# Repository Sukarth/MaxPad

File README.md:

# MaxPad
My attempt at making a utility keypad with maximum functionality! It's a 5x3 ortholinear macropad featuring a rotary encoder and OLED display, designed for context-aware developer workflows. The custom PCB uses a Xiao RP2040 with a 3x4 matrix layout. Designed in KiCad and OnShape. The full KiCad project files are included in this repository inside [MaxPadProject.zip](MaxPadProject.zip).

Check out the custom built desktop companion/customization app for the MaxPad here: https://github.com/Sukarth/MaxPadApp 

## Images

### MaxPad Case

### MaxPad Full Assembly

### MaxPad PCB Schematic

### MaxPad PCB

### Rendered MaxPad PCB (3D)

## License
MIT. See [LICENSE](LICENSE) for more details.

## Support

If this project helps or saves you time, consider supporting my work, as it keeps projects like this free, open source, and maintained:

Can't donate? Starring the repo ⭐, reporting bugs, and sharing the project help just as much!

---

Built with ❤️ by Sukarth

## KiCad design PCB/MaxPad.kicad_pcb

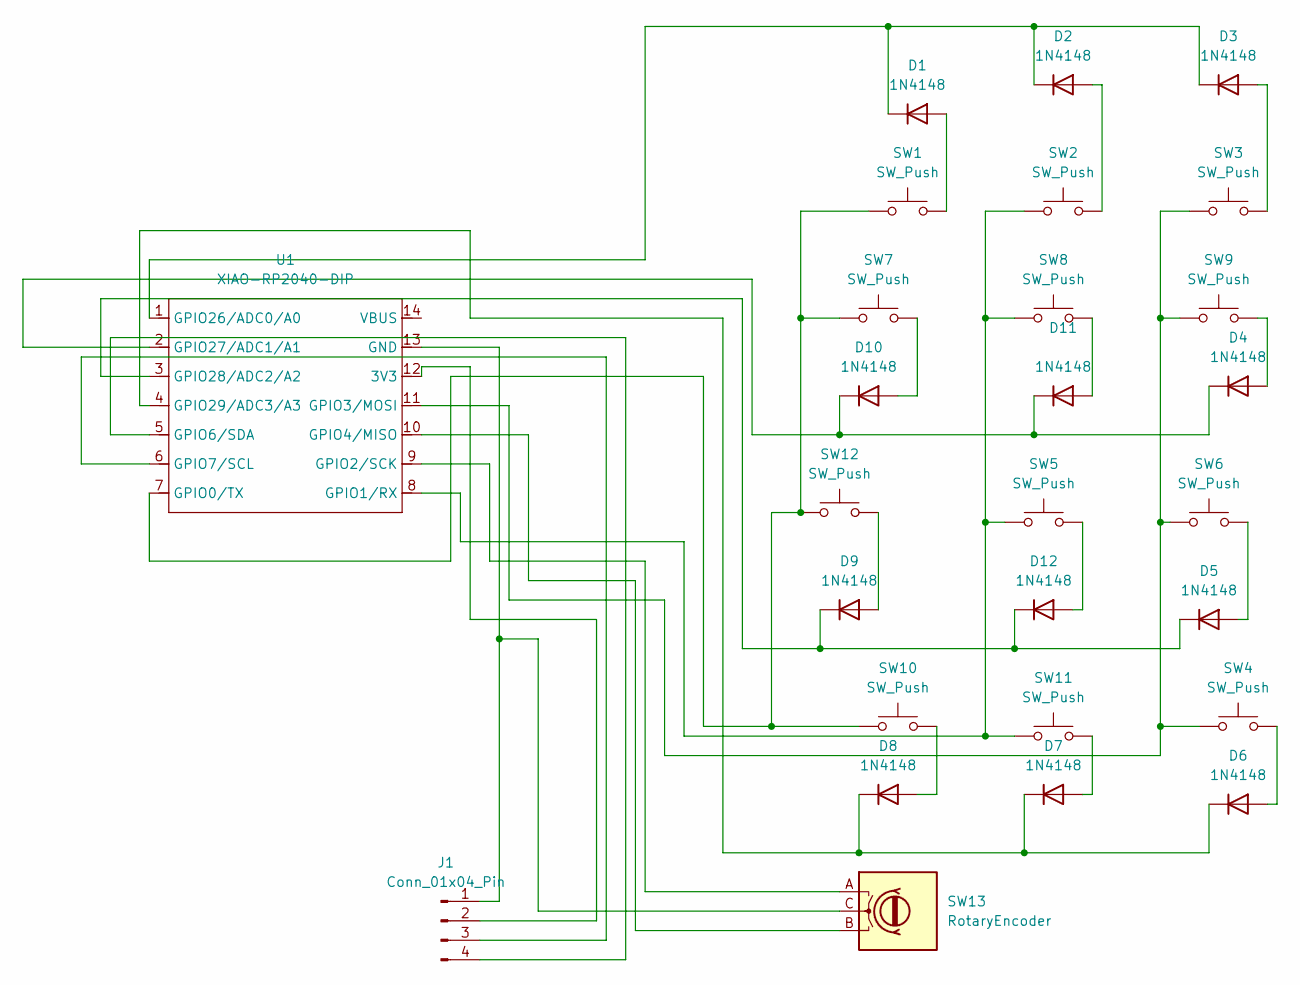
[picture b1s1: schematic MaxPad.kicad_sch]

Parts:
D1, D2, D3, D4, D5, D6, D7, D8, D9, D10, D11, D12: 1N4148; D_DO-35_SOD27_P7.62mm_Horizontal
J1: Conn_01x04_Pin; PinHeader_1x04_P2.54mm_Vertical
SW1, SW2, SW3, SW4, SW5, SW6, SW7, SW8, SW9, SW10, SW11, SW12: SW_Push; SW_Cherry_MX_1.00u_PCB
SW13: RotaryEncoder; RotaryEncoder_Alps_EC11E-Switch_Vertical_H20mm
U1: XIAO-RP2040-DIP

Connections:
unnamed: D1.2 (A), SW1.2
unnamed: D1.1 (K), D2.1 (K), D3.1 (K), U1.1 (GPIO26/ADC0/A0)
unnamed: D2.2 (A), SW2.2
unnamed: D3.2 (A), SW3.2
unnamed: D4.2 (A), SW9.2
unnamed: D5.2 (A), SW6.2
unnamed: D6.2 (A), SW4.2
unnamed: D6.1 (K), D7.1 (K), D8.1 (K), U1.4 (GPIO29/ADC3/A3)
unnamed: D7.2 (A), SW11.2
unnamed: D8.2 (A), SW10.2
unnamed: D9.2 (A), SW12.2
unnamed: D10.2 (A), SW7.2
unnamed: D4.1 (K), D10.1 (K), D11.1 (K), U1.2 (GPIO27/ADC1/A1)
unnamed: D11.2 (A), SW8.2
unnamed: D12.2 (A), SW5.2
unnamed: D5.1 (K), D9.1 (K), D12.1 (K), U1.3 (GPIO28/ADC2/A2)
unnamed: J1.1, SW13.C, U1.13 (GND)
unnamed: J1.2, U1.12 (3V3)
unnamed: J1.3, U1.6 (GPIO7/SCL)
unnamed: J1.4, U1.5 (GPIO6/SDA)
unnamed: SW1.1, SW7.1, SW10.1, SW12.1, U1.7 (GPIO0/TX)
unnamed: SW2.1, SW5.1, SW8.1, SW11.1, U1.8 (GPIO1/RX)
unnamed: SW13.A, U1.9 (GPIO2/SCK)
unnamed: SW3.1, SW4.1, SW6.1, SW9.1, U1.11 (GPIO3/MOSI)
unnamed: SW13.B, U1.10 (GPIO4/MISO)

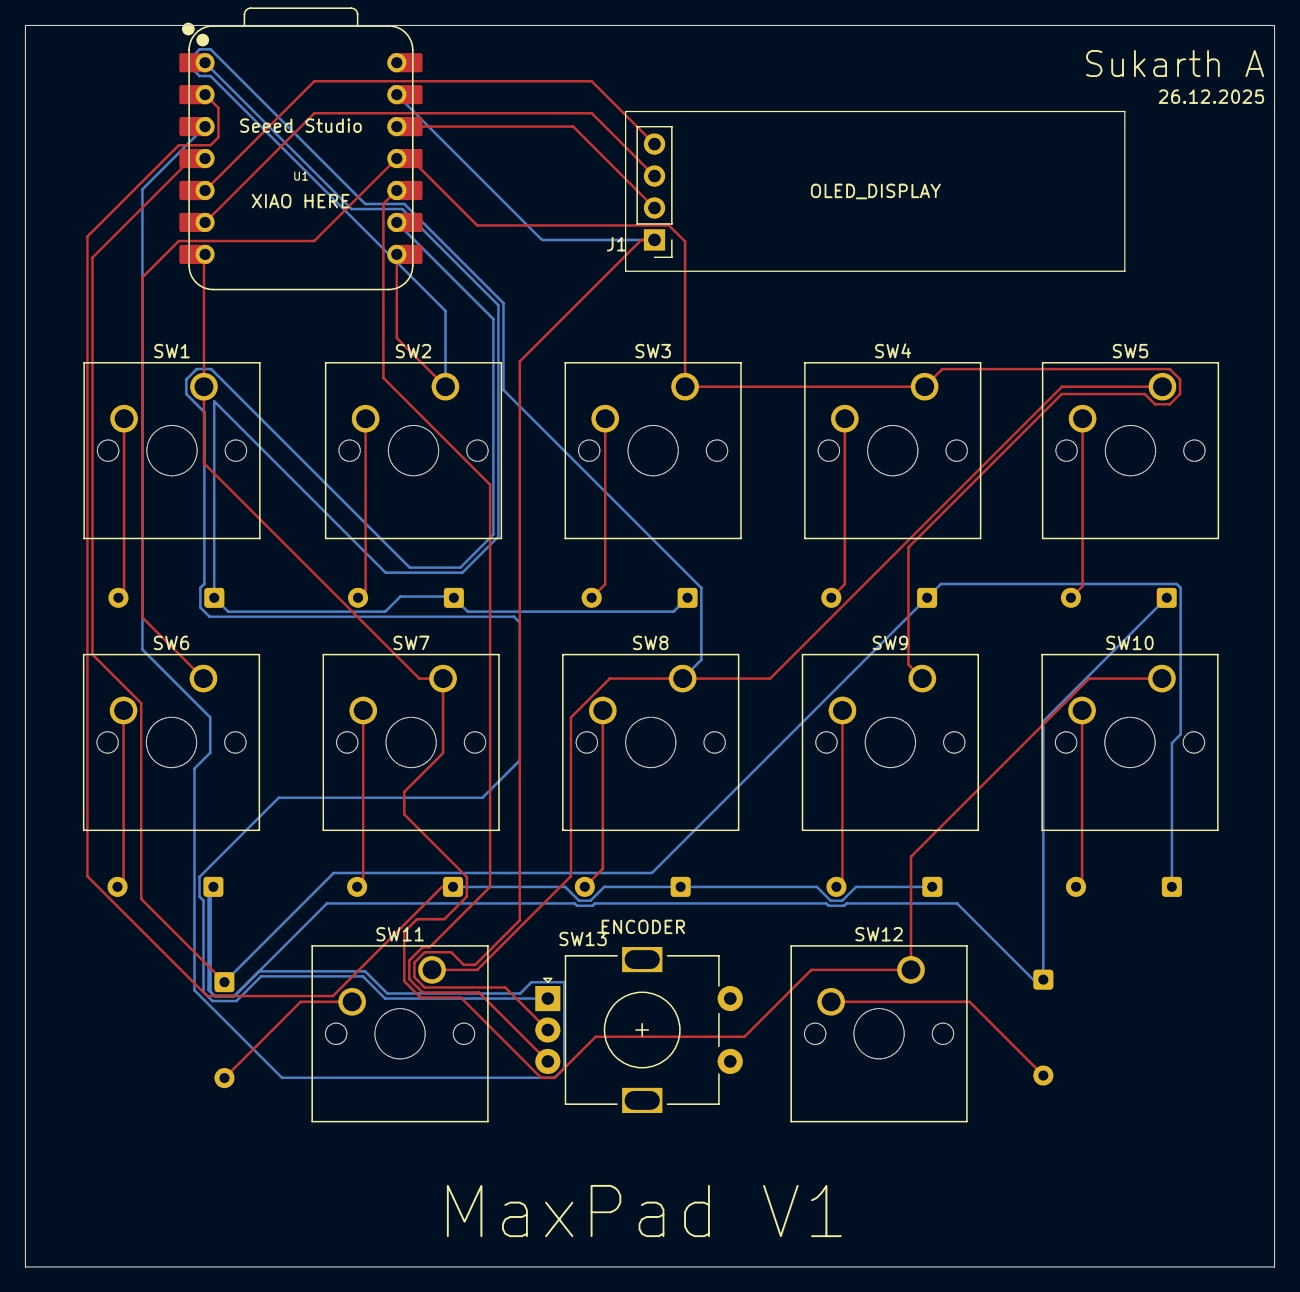
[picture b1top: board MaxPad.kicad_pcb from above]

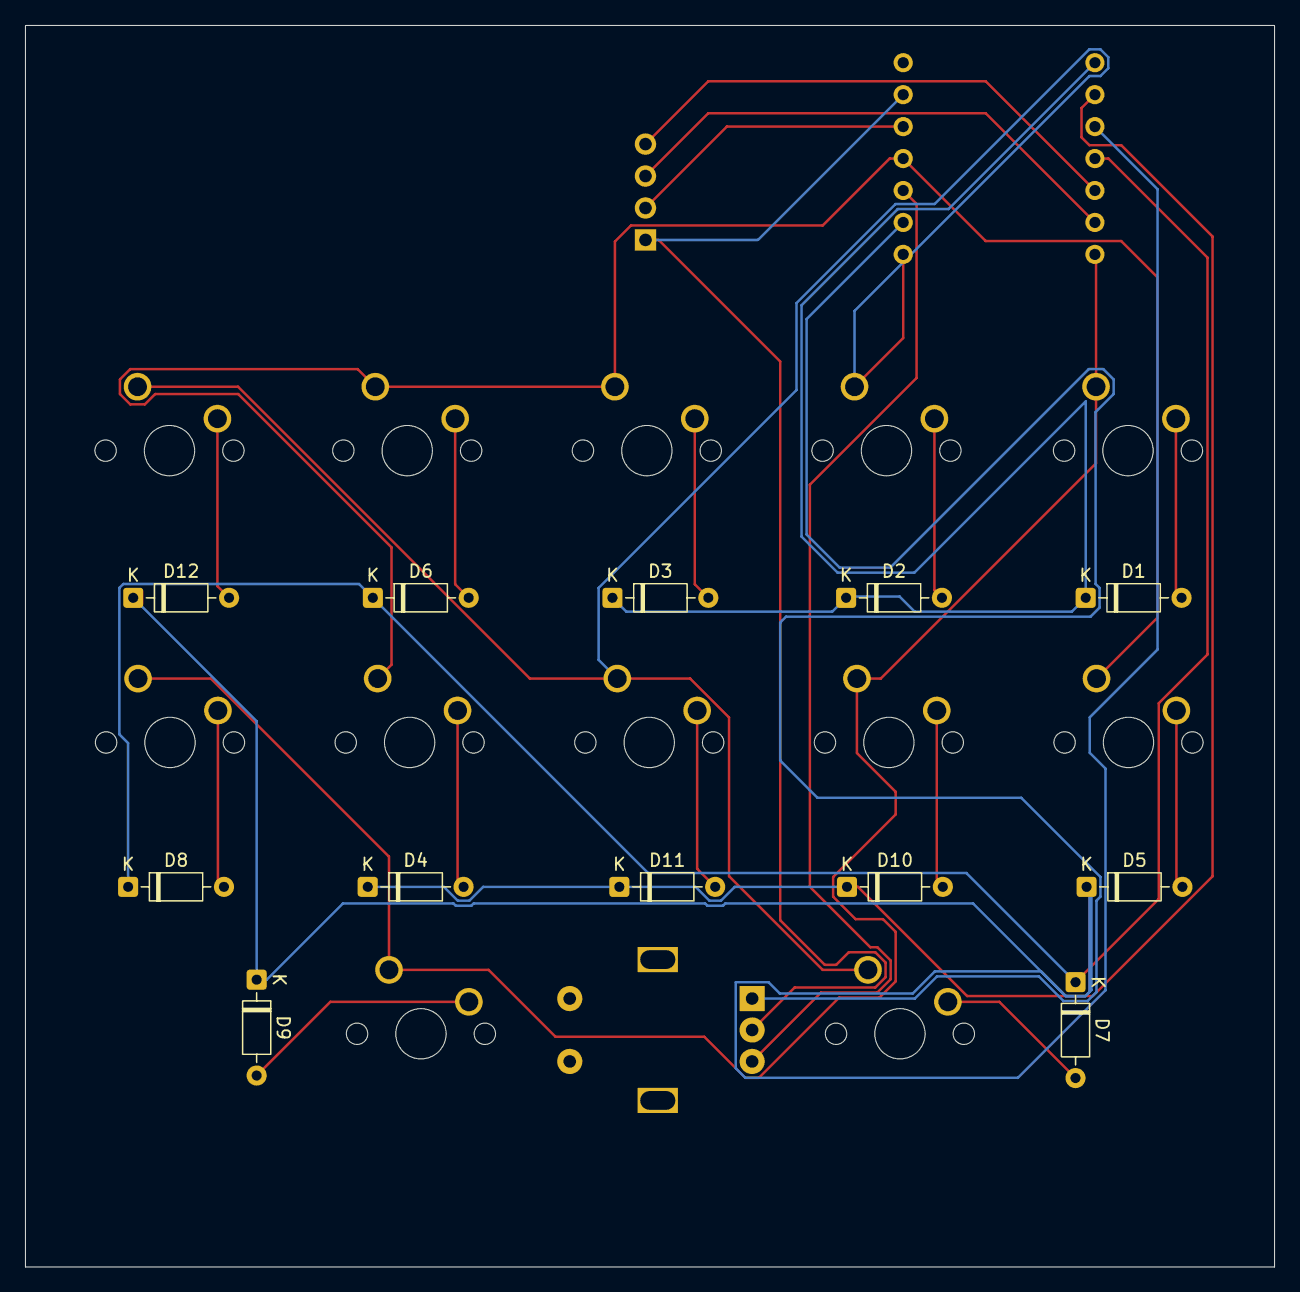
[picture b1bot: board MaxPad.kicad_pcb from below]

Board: 2 copper layers, 99.3 x 98.7 mm, 27 parts (12 on the bottom side), 25 nets.

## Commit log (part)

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2025-12-28 Update README with images of MaxPad
    Added images of the MaxPad case and PCB to README.
2026-01-15 Organization
2026-01-30 Update to stay within max PCB size requirements
2026-01-30 Adding sufficient gap and using labels in schematic
2026-03-16 Refactor OLED setup and add telemetry features
2026-05-28 added 3D printing ready files
